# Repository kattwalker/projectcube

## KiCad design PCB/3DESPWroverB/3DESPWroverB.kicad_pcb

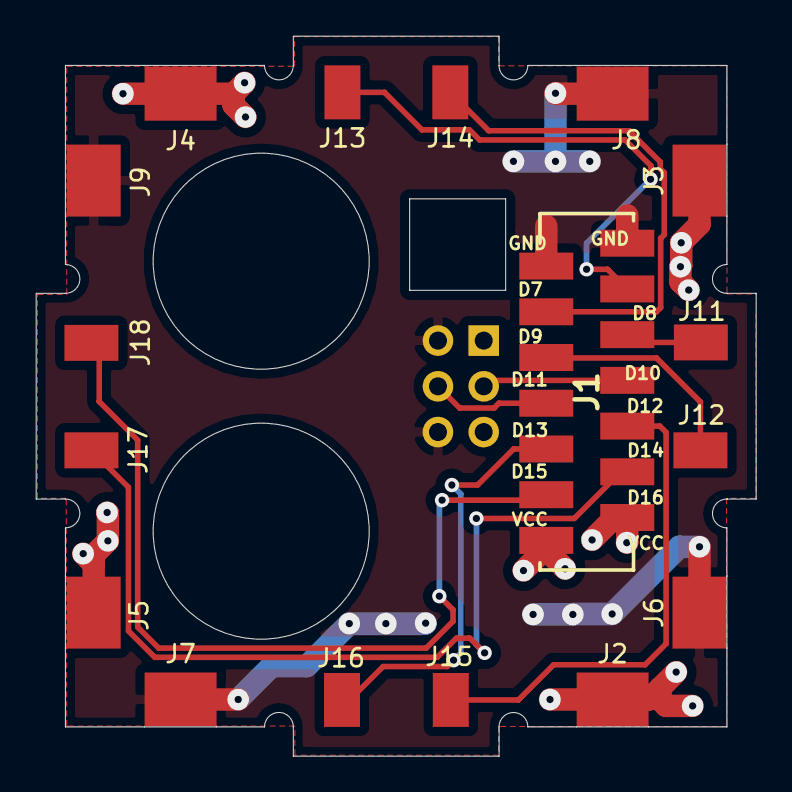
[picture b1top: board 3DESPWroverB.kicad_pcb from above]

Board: 2 copper layers, 40.0 x 40.0 mm, 18 parts (1 on the bottom side), 12 nets.

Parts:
J1: Conn_02x07_Odd_Even; TE_Micromatch_2,54_14_SMD
J2, J3, J4, J5, J6, J7, J8, J9: Conn_01x01; CubeSidePad
J10: Conn_02x03_Odd_Even; PinHeader_2x03_P2.54mm_Vertical
J11, J12, J13, J14, J15, J16, J17, J18: Conn_01x01; CubeCenterPad

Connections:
/D7: J1.3, J13.1
/D8: J1.4, J14.1
/D9: J1.5, J11.1
/D10: J1.6, J12.1
/D11: J1.7, J10.3
/D12: J1.8, J10.4
/D13: J1.9, J15.1
/D14: J1.10, J16.1
/D15: J1.11, J17.1
/D16: J1.12, J18.1
GND: J1.1, J1.2, J6.1, J7.1, J8.1, J9.1, J10.2, J10.6
VCC: J1.13, J1.14, J2.1, J3.1, J4.1, J5.1, J10.1, J10.5

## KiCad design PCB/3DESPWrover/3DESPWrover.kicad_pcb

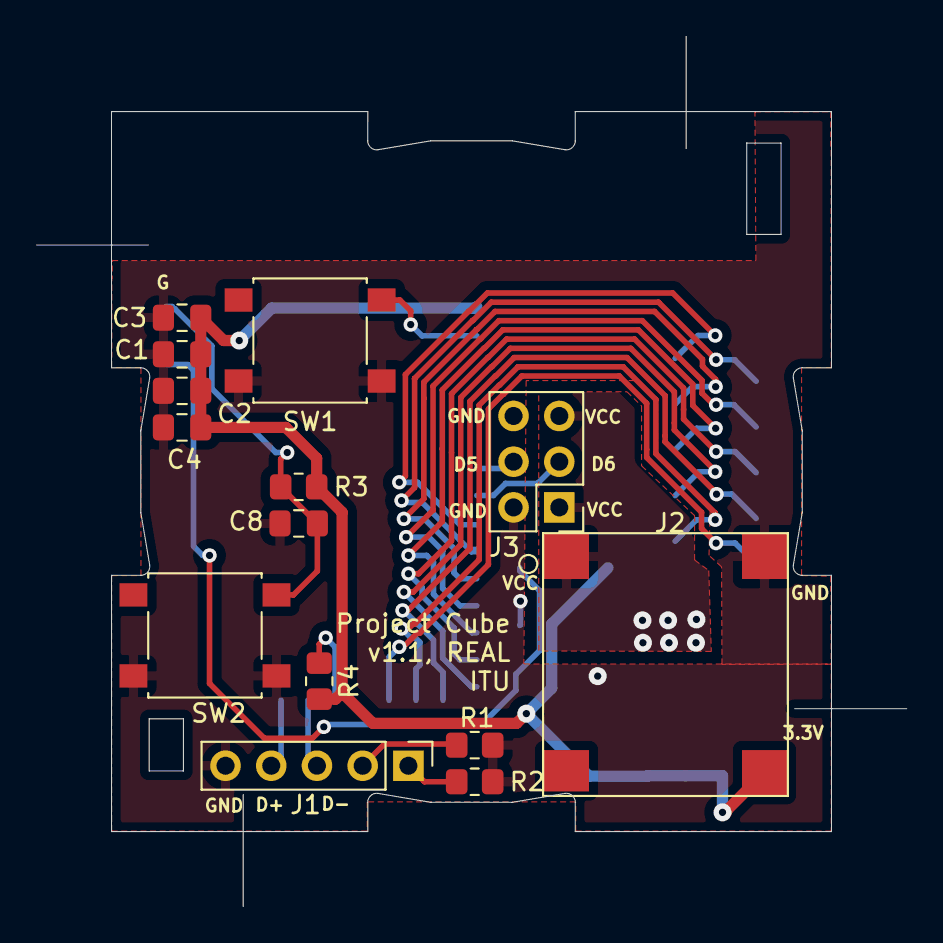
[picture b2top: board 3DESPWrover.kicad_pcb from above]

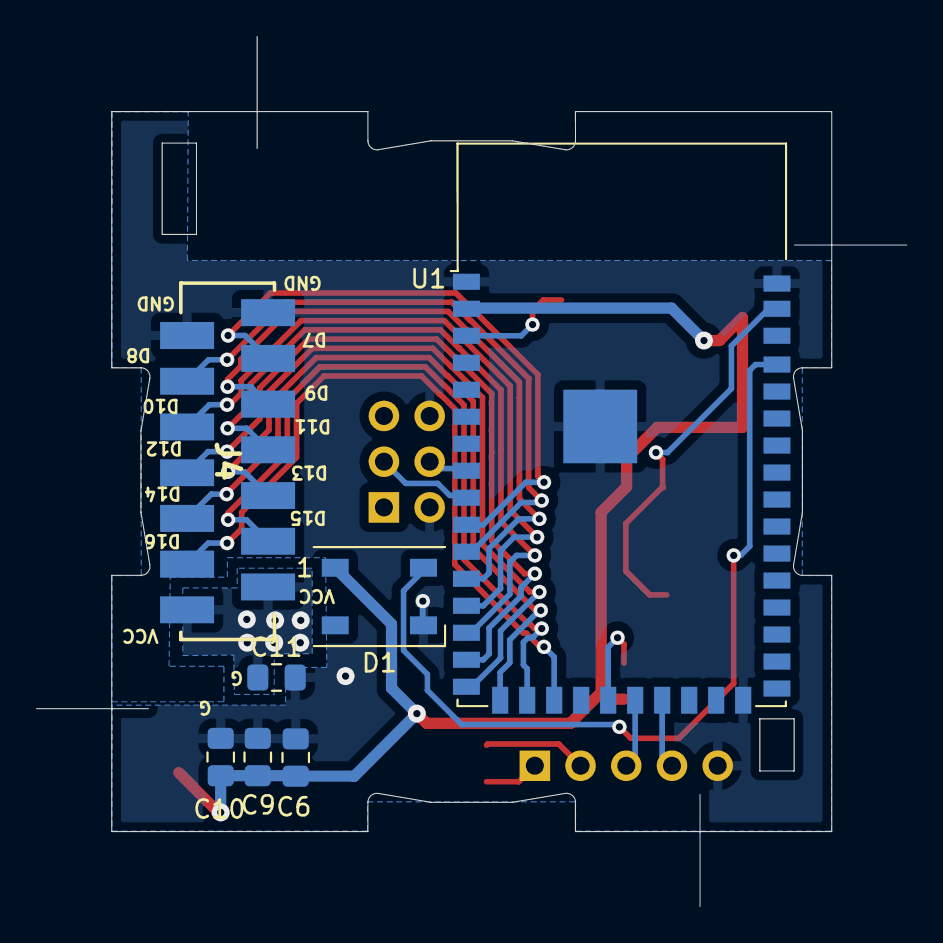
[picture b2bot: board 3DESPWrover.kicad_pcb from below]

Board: 2 copper layers, 40.0 x 40.0 mm, 21 parts (7 on the bottom side), 23 nets.

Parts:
C1, C2, C3, C4, C11: 10u; C_0805_2012Metric_Pad1.18x1.45mm_HandSolder
C6: 0.1u; C_0805_2012Metric_Pad1.18x1.45mm_HandSolder
C8: 1u; C_0805_2012Metric_Pad1.18x1.45mm_HandSolder
C9, C10: 22u; C_0805_2012Metric_Pad1.18x1.45mm_HandSolder
D1: WS2812B; LED_WS2812B_PLCC4_5.0x5.0mm_P3.2mm
J1: Conn_01x05_Male; PinHeader_1x05_P2.54mm_Vertical
J2: Conn_01x04; K7803JT-500R3-SMD
J3: Conn_02x03_Odd_Even; PinHeader_2x03_P2.54mm_Vertical
J4: Conn_02x07_Odd_Even; TE_Micromatch_2,54_14_SMD
R1, R2: 5.1k; R_0805_2012Metric_Pad1.20x1.40mm_HandSolder
R3, R4: 10k; R_0805_2012Metric_Pad1.20x1.40mm_HandSolder
SW1, SW2: SW_Push; SW_SPST_B3S-1000
U1: ESP32-S2-WROVER

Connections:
+3V3: C1.1, C2.1, C3.1, C4.1, C6.1, C9.1, C10.1, D1.1, J2.3, R3.1, R4.2, U1.2
/AD1: R4.1, U1.21
/BOOT0: SW1.2, U1.3
/D5: J3.4, U1.8
/D6: J3.3, U1.9
/D7: J4.3, U1.10
/D8: J4.4, U1.11
/D9: J4.5, U1.12
/D10: J4.6, U1.13
/D11: J4.7, U1.14
/D12: J4.8, U1.15
/D13: J4.9, U1.16
/D14: J4.10, U1.17
/D15: J4.11, U1.18
/D16: J4.12, U1.19
/D+: J1.4, U1.23
/D-: J1.3, U1.22
/NEOPIX: D1.4, U1.39
/RESET: C8.1, R3.2, SW2.2, U1.41
/Vin: C11.1, J2.1, J3.1, J3.5, J4.13, J4.14
GND: C1.2, C2.2, C3.2, C4.2, C6.2, C8.2, C9.2, C10.2, C11.2, D1.3, J1.5, J2.2, J3.2, J3.6, J4.1, J4.2, R1.2, R2.2, SW1.1, SW2.1, U1.1, U1.26, U1.42, U1.43
unnamed: J1.1, R2.1
unnamed: J1.2, R1.1

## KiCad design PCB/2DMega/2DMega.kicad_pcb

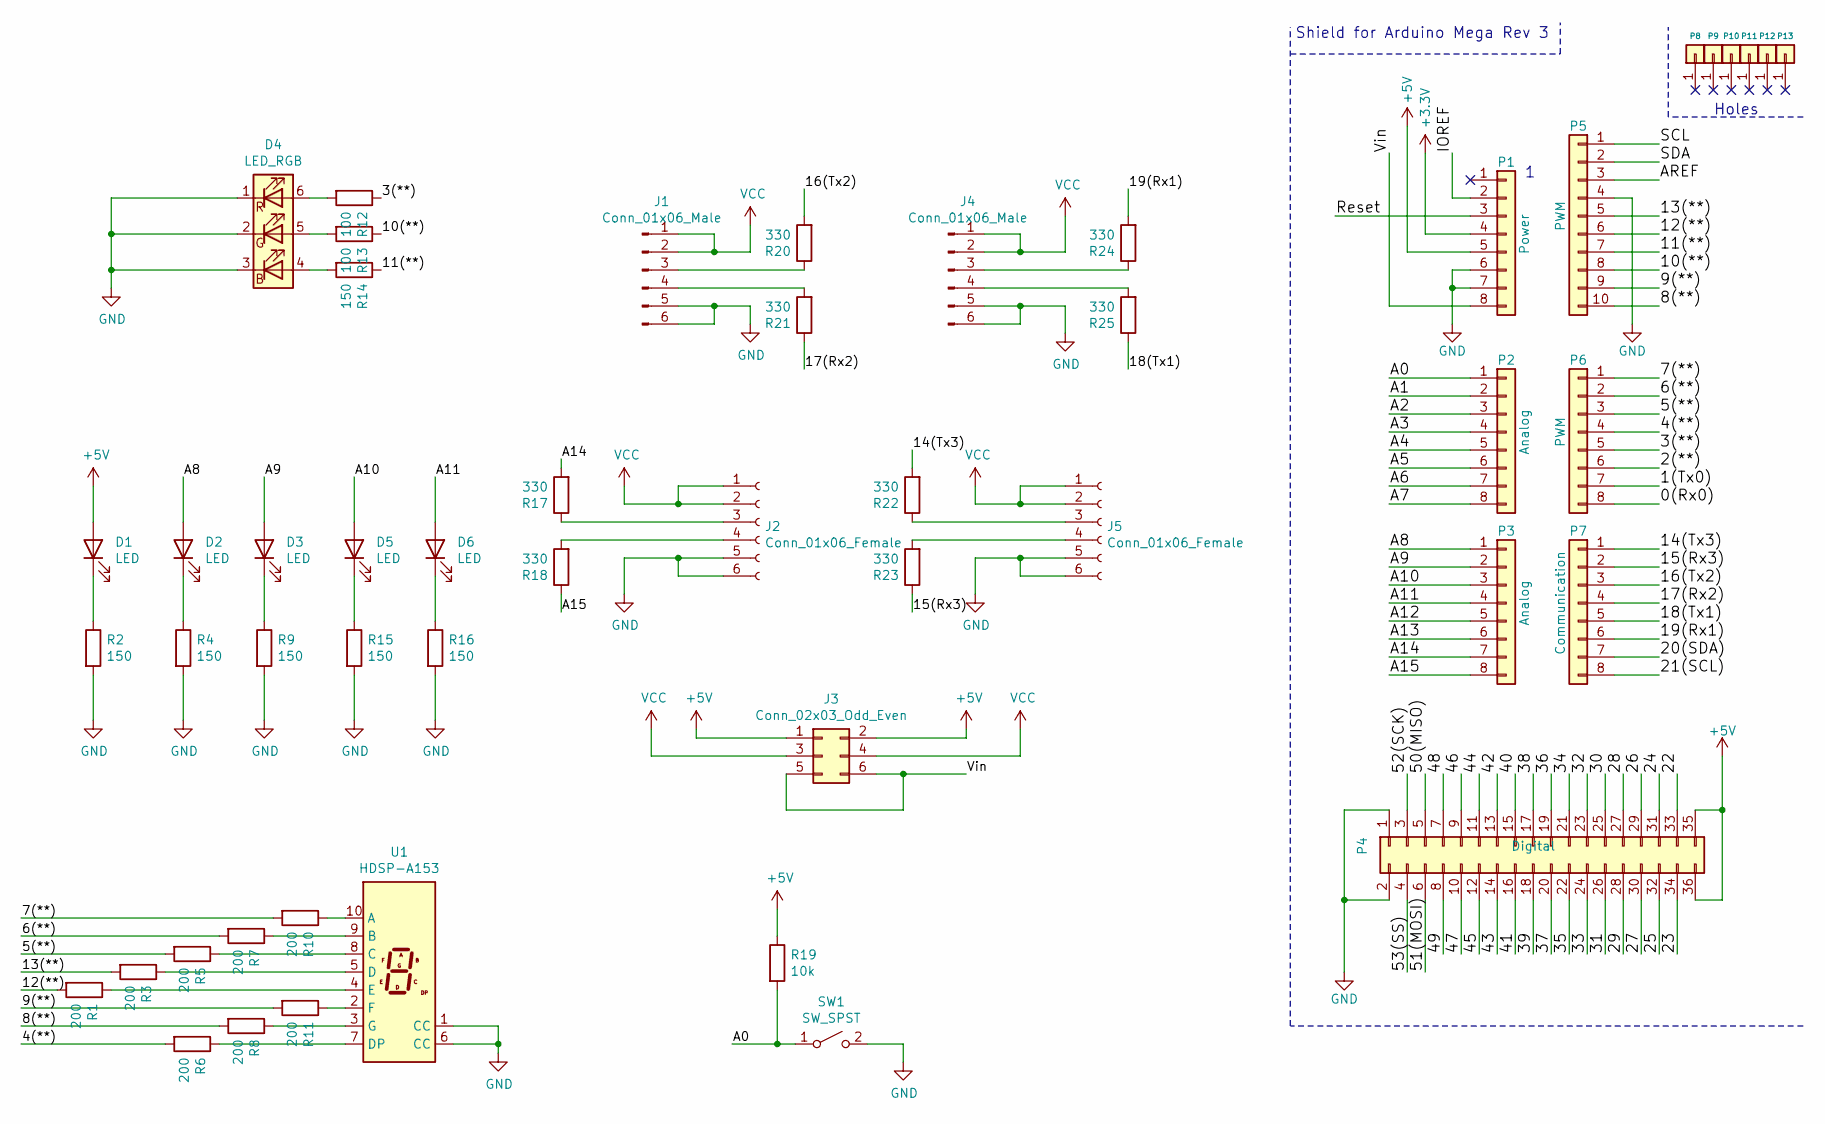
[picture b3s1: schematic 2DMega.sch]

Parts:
D1, D2, D3, D5, D6: LED; LED_0805_2012Metric_Pad1.15x1.40mm_HandSolder
D4: LED_RGB; LED_Avago_PLCC6_3x2.8mm
J1, J4: Conn_01x06_Male; PinHeader_1x06_P2.54mm_Horizontal
J2, J5: Conn_01x06_Female; PinSocket_1x06_P2.54mm_Horizontal
J3: Conn_02x03_Odd_Even; PinHeader_2x03_P2.54mm_Vertical
P1: Power; Socket_Strip_Arduino_2x18
P2, P3: Analog; Socket_Strip_Arduino_1x08
P4: Digital; Socket_Strip_Arduino_1x08
P5: PWM; Socket_Strip_Arduino_1x10
P6: PWM; Socket_Strip_Arduino_1x08
P7: Communication; Socket_Strip_Arduino_1x08
P8, P9, P10, P11, P12, P13: CONN_01X01; Arduino_1pin
R1, R3, R5, R6, R7, R8, R10, R11: 200; R_0805_2012Metric_Pad1.20x1.40mm_HandSolder
R2, R4, R9, R14, R15, R16: 150; R_0805_2012Metric_Pad1.20x1.40mm_HandSolder
R12, R13: 100; R_0805_2012Metric_Pad1.20x1.40mm_HandSolder
R17, R18, R20, R21, R22, R23, R24, R25: 330; R_0805_2012Metric_Pad1.20x1.40mm_HandSolder
R19: 10k; R_0805_2012Metric_Pad1.20x1.40mm_HandSolder
SW1: SW_SPST; SW_SPST_B3S-1000
U1: HDSP-A153; Sx39-1xxxxx

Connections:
+3V3: P1.4
+5V: D1.2 (A), J3.1, J3.2, P1.5, P4.35, P4.36, R19.1
/0(Rx0): P6.8
/1(Tx0): P6.7
/2(**): P6.6
/3(**): P6.5, R12.1
/4(**): P6.4, R6.2
/5(**): P6.3, R5.2
/6(**): P6.2, R7.2
/7(**): P6.1, R10.2
/8(**): P5.10, R8.2
/9(**): P5.9, R11.2
/10(**): P5.8, R13.1
/11(**): P5.7, R14.1
/12(**): P5.6, R1.2
/13(**): P5.5, R3.2
/14(Tx3): P7.1, R22.2
/15(Rx3): P7.2, R23.1
/16(Tx2): P7.3, R20.2
/17(Rx2): P7.4, R21.1
/18(Tx1): P7.5, R25.1
/19(Rx1): P7.6, R24.2
/20(SDA): P7.7
/21(SCL): P7.8
/22: P4.33
/23: P4.34
/24: P4.31
/25: P4.32
/26: P4.29
/27: P4.30
/28: P4.27
/29: P4.28
/30: P4.25
/31: P4.26
/32: P4.23
/33: P4.24
/34: P4.21
/35: P4.22
/36: P4.19
/37: P4.20
/38: P4.17
/39: P4.18
/40: P4.15
/41: P4.16
/42: P4.13
/43: P4.14
/44: P4.11
/45: P4.12
/46: P4.9
/47: P4.10
/48: P4.7
/49: P4.8
/50(MISO): P4.5
/51(MOSI): P4.6
/52(SCK): P4.3
/53(SS): P4.4
/A0: P2.1, R19.2, SW1.1 (A)
/A1: P2.2
/A2: P2.3
/A3: P2.4
/A4: P2.5
/A5: P2.6
/A6: P2.7
/A7: P2.8
/A8: D2.2 (A), P3.1
/A9: D3.2 (A), P3.2
/A10: D5.2 (A), P3.3
/A11: D6.2 (A), P3.4
/A12: P3.5
/A13: P3.6
/A14: P3.7, R17.2
/A15: P3.8, R18.1
/AREF: P5.3
/IOREF: P1.2
/Reset: P1.3
/SCL: P5.1
/SDA: P5.2
/Vin: J3.5, J3.6, P1.8
GND: D4.1 (RK), D4.2 (GK), D4.3 (BK), J1.5, J1.6, J2.5, J2.6, J4.5, J4.6, J5.5, J5.6, P1.6, P1.7, P4.1, P4.2, P5.4, R2.2, R4.2, R9.2, R15.2, R16.2, SW1.2 (B), U1.1 (CC), U1.6 (CC)
unnamed: D1.1 (K), R2.1
unnamed: D2.1 (K), R4.1
unnamed: D3.1 (K), R9.1
unnamed: D4.4 (BA), R14.2
unnamed: D4.5 (GA), R13.2
unnamed: D4.6 (RA), R12.2
unnamed: D5.1 (K), R15.1
unnamed: D6.1 (K), R16.1
unnamed: J1.3, R20.1
unnamed: J1.4, R21.2
unnamed: J2.3, R17.1
unnamed: J2.4, R18.2
unnamed: J4.3, R24.1
unnamed: J4.4, R25.2
unnamed: J5.3, R22.1
unnamed: J5.4, R23.2
unnamed: R1.1, U1.4 (E)
unnamed: R3.1, U1.5 (D)
unnamed: R5.1, U1.8 (C)
unnamed: R6.1, U1.7 (DP)
unnamed: R7.1, U1.9 (B)
unnamed: R8.1, U1.3 (G)
unnamed: R10.1, U1.10 (A)
unnamed: R11.1, U1.2 (F)
VCC: J1.1, J1.2, J2.1, J2.2, J3.3, J3.4, J4.1, J4.2, J5.1, J5.2

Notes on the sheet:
Shield for Arduino Mega Rev 3
Holes

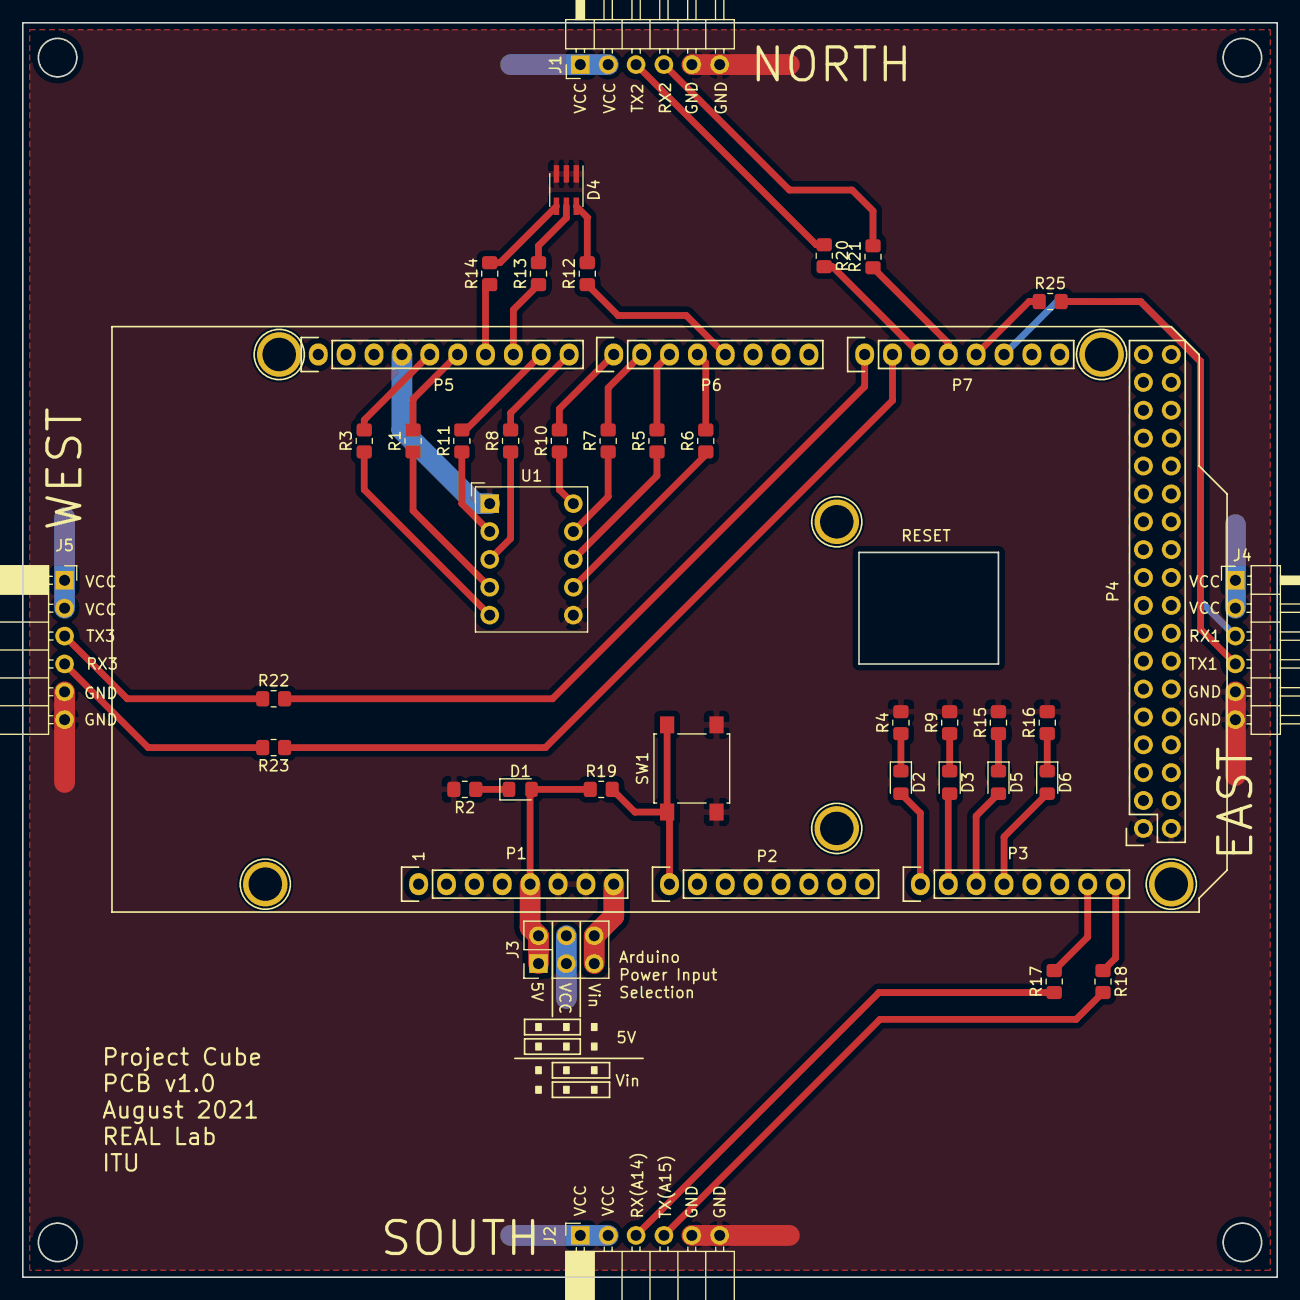
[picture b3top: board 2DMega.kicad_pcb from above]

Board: 2 copper layers, 114.3 x 114.3 mm, 51 parts (1 on the bottom side), 52 nets.

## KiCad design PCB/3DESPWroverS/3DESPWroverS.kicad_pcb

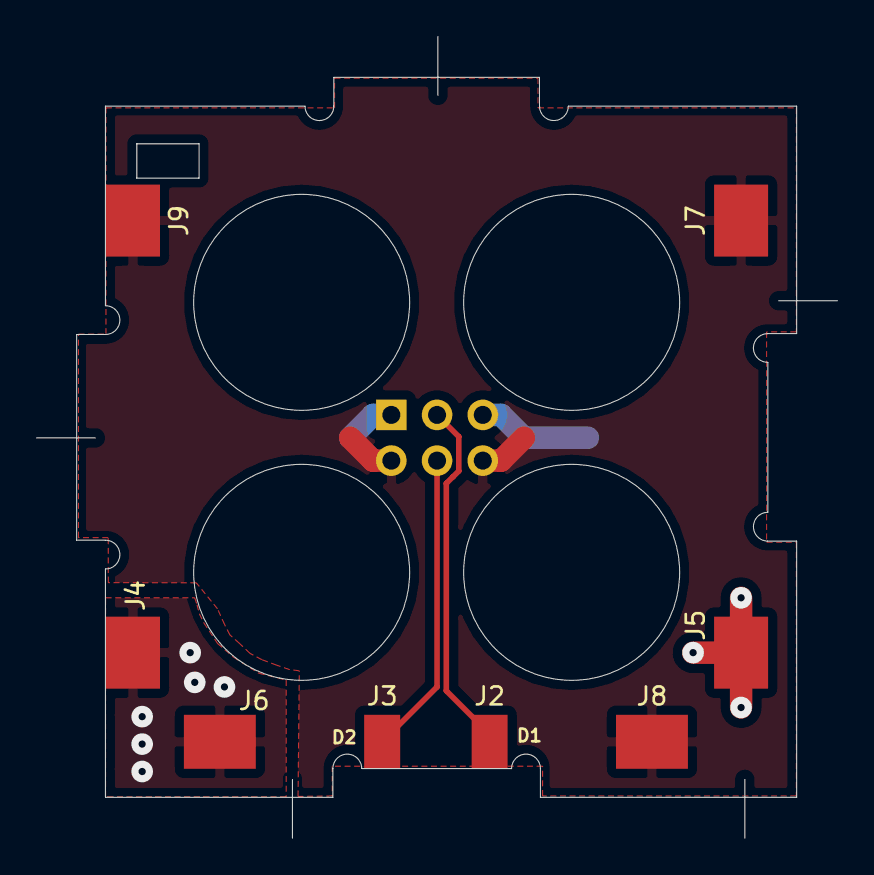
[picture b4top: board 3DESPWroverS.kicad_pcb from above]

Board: 2 copper layers, 40.0 x 40.0 mm, 9 parts (1 on the bottom side), 4 nets.

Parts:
J1: Conn_02x03_Odd_Even; PinHeader_2x03_P2.54mm_Vertical
J2, J3: Conn_01x01; CubeCenterPad
J4, J5, J6, J7, J8, J9: Conn_01x01; CubeSidePad

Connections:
/D1: J1.3, J2.1
/D2: J1.4, J3.1
GND: J1.2, J1.6, J7.1, J8.1, J9.1
VCC: J1.1, J1.5, J4.1, J5.1, J6.1

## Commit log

2021-10-14 Add files via upload
    CODE WORKING FOR 1,7, AND 4
